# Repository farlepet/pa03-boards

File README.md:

PA03 Boards
===========

PCB designs based on the PA03 op-amp

Footprint for the PA03 is designed to work with Preci-Dip 15111-81-3920

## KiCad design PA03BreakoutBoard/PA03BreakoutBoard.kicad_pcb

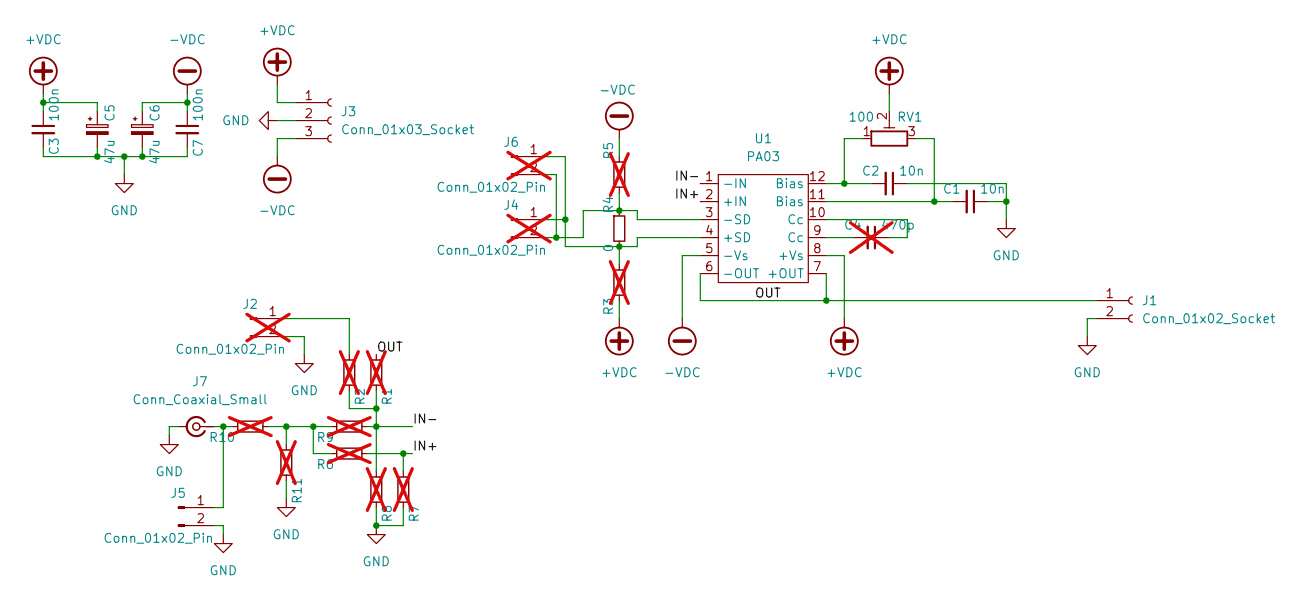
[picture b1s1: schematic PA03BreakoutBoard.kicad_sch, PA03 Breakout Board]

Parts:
C1, C2: 10n; C_0603_1608Metric
C3, C7: 100n; C_0603_1608Metric
C4: 470p; C_0603_1608Metric; not fitted
C5, C6: 47u; CP_Elec_8x10
J1: Conn_01x02_Socket; PhoenixContact_MSTBA_2,5_2-G-5,08_1x02_P5.08mm_Horizontal
J2, J6: Conn_01x02_Pin; PhoenixContact_MC_1,5_2-G-3.81_1x02_P3.81mm_Horizontal; not fitted
J3: Conn_01x03_Socket; PhoenixContact_MSTBA_2,5_3-G-5,08_1x03_P5.08mm_Horizontal
J4: Conn_01x02_Pin; PinHeader_1x02_P2.54mm_Vertical; not fitted
J5: Conn_01x02_Pin; PhoenixContact_MC_1,5_2-G-3.81_1x02_P3.81mm_Horizontal
J7: Conn_Coaxial_Small; Generic_SMA_BoardEdge
R1, R2, R3, R5, R6, R7, R8, R9, R10, R11: R_0603_1608Metric; not fitted
R4: 0; R_0603_1608Metric
RV1: 100; Potentiometer_Bourns_TC33X_Vertical
U1: PA03

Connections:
+VDC: C3.1, C5.1, J3.1, R3.2, RV1.2, U1.8 (+Vs)
-VDC: C6.1, C7.1, J3.3, R5.1, U1.5 (-Vs)
/IN+: R6.2, R7.2, U1.2 (+IN)
/IN-: R1.1, R2.1, R8.2, R9.2, U1.1 (-IN)
/OUT: J1.1, R1.2, U1.6 (-OUT), U1.7 (+OUT)
GND: C1.1, C2.1, C3.2, C5.2, C6.2, C7.2, J1.2, J2.2, J3.2, J5.2, J7.2 (Ext), R7.1, R8.1, R11.1
unnamed: C4.1, U1.10 (Cc)
unnamed: C4.2, U1.9 (Cc)
unnamed: C2.2, RV1.1, U1.12 (Bias)
unnamed: C1.2, RV1.3, U1.11 (Bias)
unnamed: J4.1, J6.1, R3.1, R4.2, U1.4 (+SD)
unnamed: J4.2, J6.2, R4.1, R5.2, U1.3 (-SD)
unnamed: J5.1, J7.1 (In), R10.1
unnamed: J2.1, R2.2
unnamed: R6.1, R9.1, R10.2, R11.2

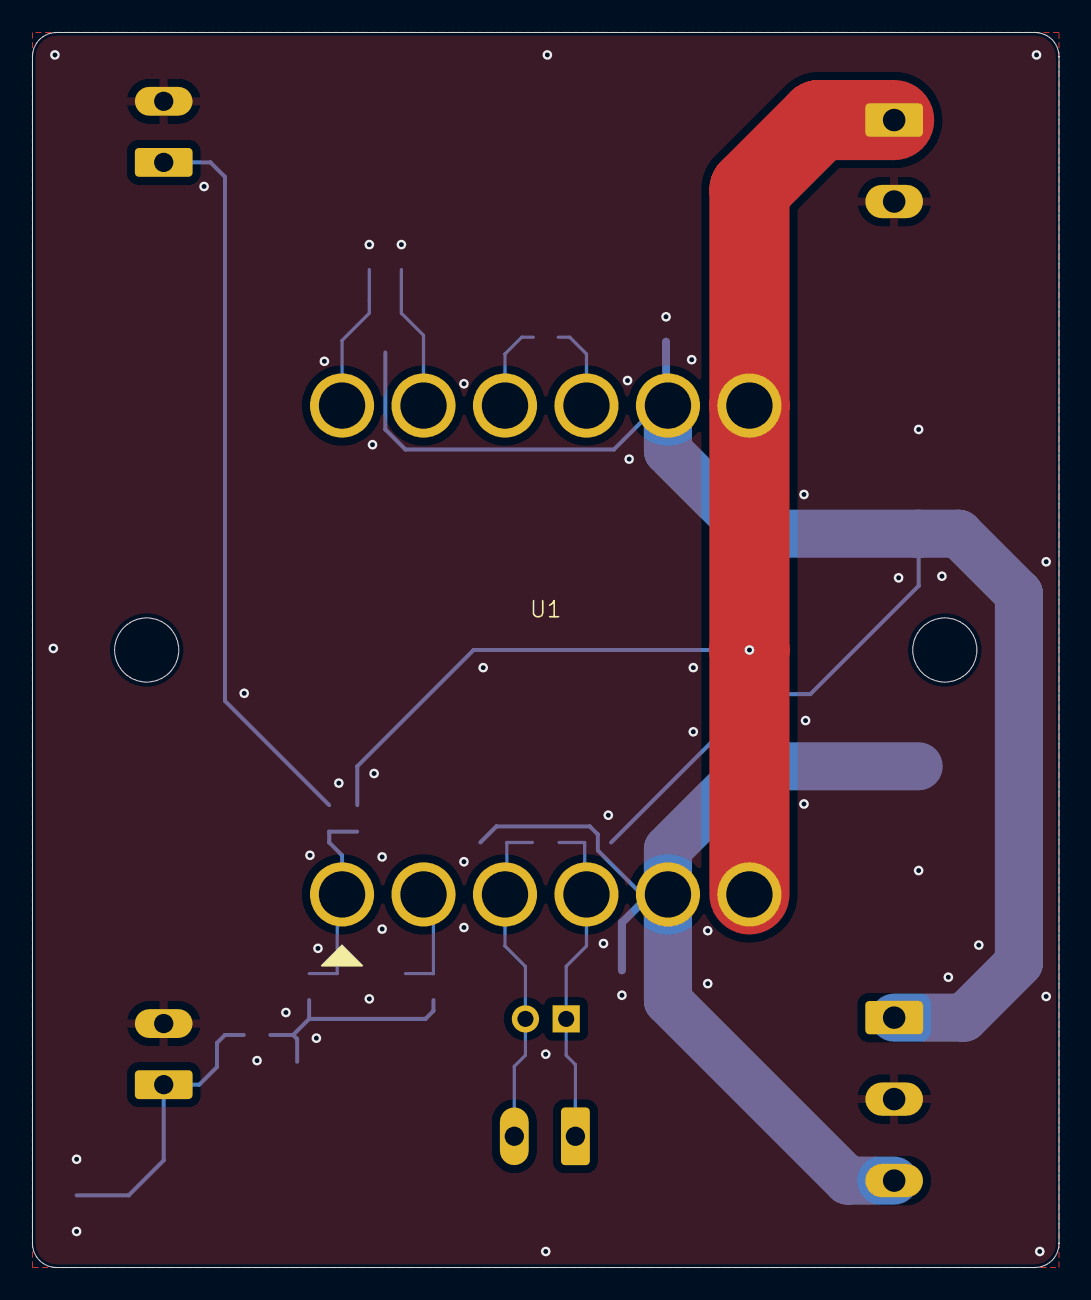
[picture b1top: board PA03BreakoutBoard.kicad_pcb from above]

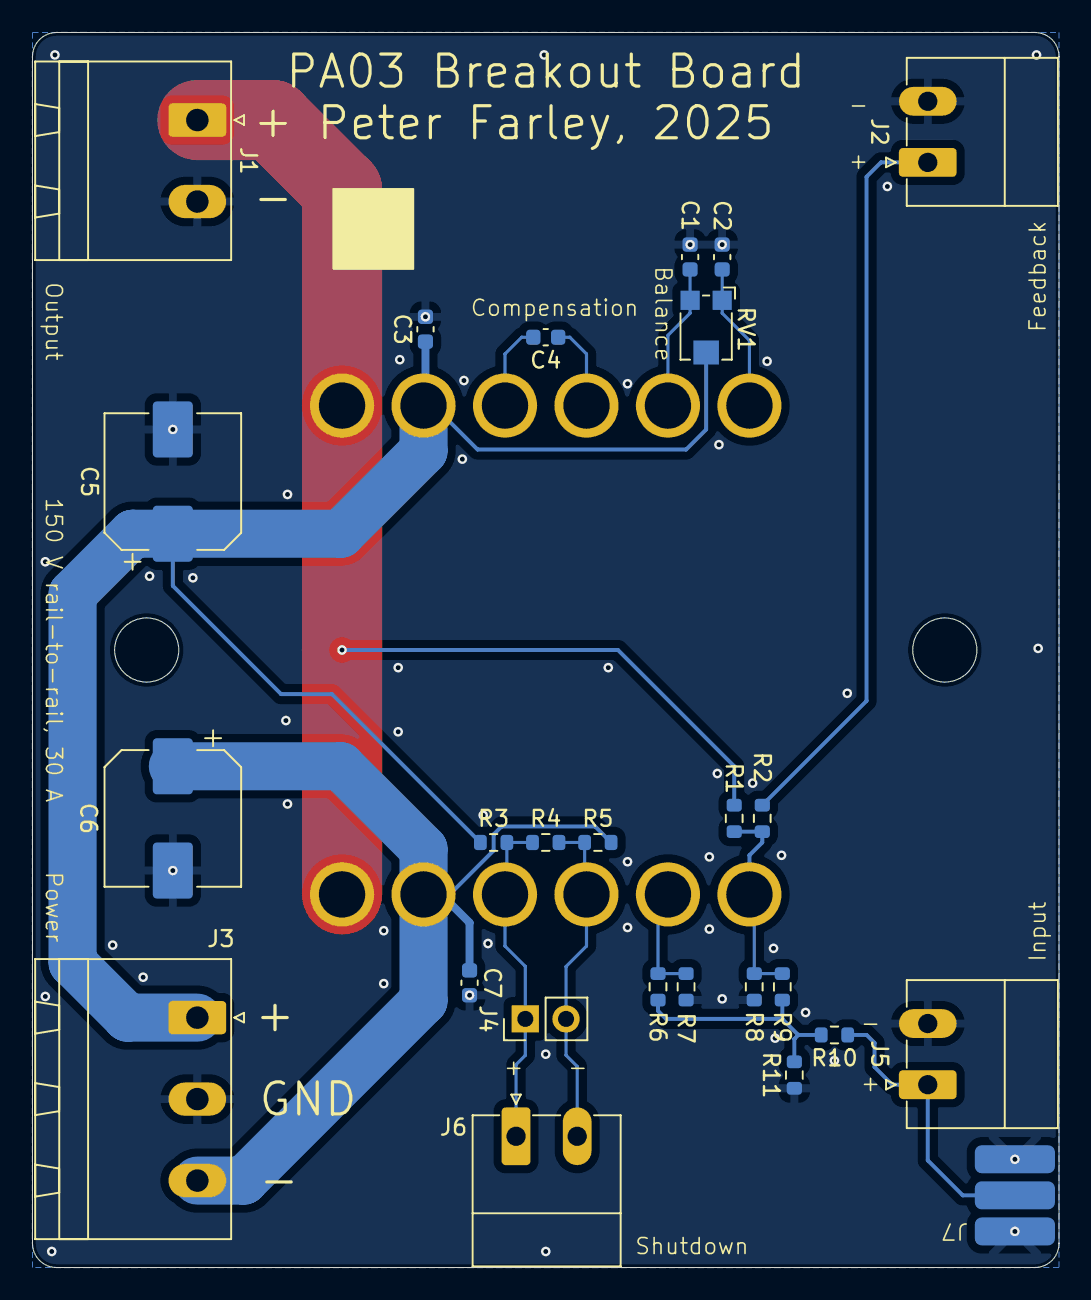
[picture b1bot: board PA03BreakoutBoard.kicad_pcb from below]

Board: 2 copper layers, 64.0 x 77.0 mm, 27 parts (26 on the bottom side), 15 nets.

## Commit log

2024-12-31 Added PA03 breakout board
2024-12-31 Add license
